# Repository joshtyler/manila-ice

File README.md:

# manila iCE

manila iCE is a credit card sized Lattice iCE40 development board.

Quick links:
* [Schematic](https://github.com/joshtyler/manila-ice/releases/download/hardware_v1.0/manila_ice-schematic.pdf)
* [Gerbers](https://github.com/joshtyler/manila-ice/releases/download/hardware_v1.0/manila_ice-fab.zip)

Features:
* Credit card sized (85x54mm)
* iCE40 HX4K FPGA (usable as an 8k device in yosys)
* Gigabit Ethernet
* 128Mbit SDRAM
* Two dual row PMODs
* 128Mbit QSPI flash
* USB UART (2Mbaud speed)
* 50MHz oscillator
* 64kbit I2C EEPROM
* 8 LEDs
* 2 push buttons
* 3A 3V3 and 1V2 power supplies

## Bootloader

The board has a bootloader which supports loading of FPGA bitstreams over UART. Four slots for bitstreams are supported. The first is reserved for the bootloader itself, and the other three can hold user images.

The FPGA is configured with the bootloader on powerup, and then automatically boots into the first bitstream after a timeout. Alternate bitstreams can be selected using the buttons, or by UART command.

## Example applications

The following applications are provided to demonstrate functionality of the PCB:
* UART loopback
* SDRAM controller
* Gigabit ethernet loopback

## Programming Application

To support uploading user applications, a Linux software utility is provided to update any of the bitstream slots.

To install the software checkout this repository, and run the following commands:
1. `cd sw/scripts`
1. `make`
1. `make install`

You will now have an executable called `manila` in your path.

To program the FPGA:
1. Plug in the board with USB
1. Press either of the switches to pause the boot process (optional if you're quick!)
1. `manila prog [path to bitstream]`

To discover the optional arguments run `manila prog` without any arguments.

## SPI Flash

The SPI flash memory is laid out as follows:

The bootloader partition is protected to prevent accidental erasure.

## Bootloader Upgrades

In order to allow for firmware upgrades the protection is volatile. When the firmware is configured with the bootloader, before UART commands are accpeted it sends commands to the SPI flash to write protect the bootloader region, and then locks out that configuration until the SPI flash is power cycled.

TODO: document process for upgrading bootloader

## PCB Errata
* v1.0 - No known issues affecting functionality
	* LEDs in ethernet phy do not light due to symbol error
	* Silkscreen box around phtograph on back does not fully enclose image after fab
	* Caption for photograph on back is difficult to read

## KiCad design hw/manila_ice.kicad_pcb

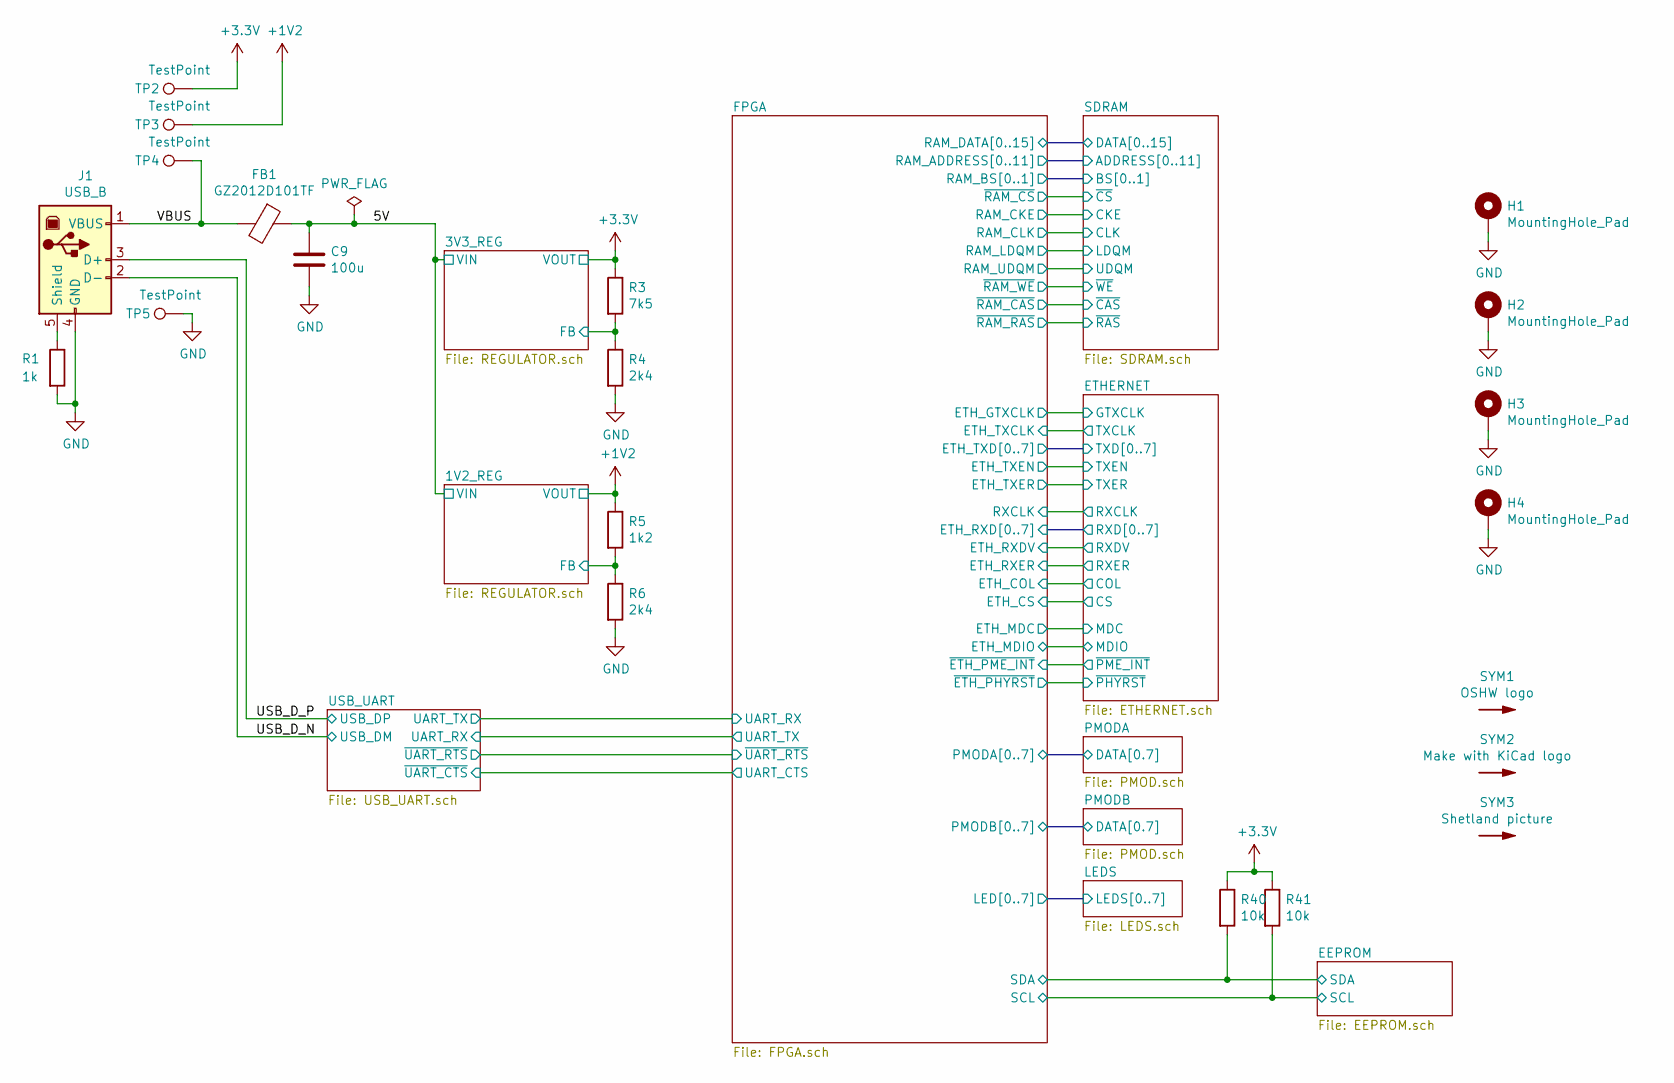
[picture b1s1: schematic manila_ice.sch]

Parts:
C9: 100u; CP_EIA-3528-21_Kemet-B; LCSC Part C16133
FB1: GZ2012D101TF; L_0805_2012Metric; LCSC Part C1015
H1, H2, H3, H4: MountingHole_Pad; MountingHole_3.2mm_M3_Pad; JLCPCB BOM 0
J1: USB_B; USB_B_OST_USB-B1HSxx_Horizontal; JLCPCB BOM 0
R1: 1k; R_0603_1608Metric; LCSC Part C21190
R3: 7k5; R_0603_1608Metric; LCSC Part C22452
R4, R6: 2k4; R_0603_1608Metric; LCSC Part C22940
R5: 1k2; R_0603_1608Metric; LCSC Part C22765
R40, R41: 10k; R_0603_1608Metric; LCSC Part C25804
SYM1: OSHW logo; OSHW-Logo_5.7x6mm_SilkScreen; JLCPCB BOM 0
SYM2: Make with KiCad logo; KiCad-Logo2_5mm_SilkScreen; JLCPCB BOM 0
SYM3: Shetland picture; Shetland_combined; JLCPCB BOM 0
TP2, TP3, TP4, TP5: TestPoint; TestPoint_Pad_D1.0mm; JLCPCB BOM 0

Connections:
+1V2: R5.1, TP3.1; also elsewhere on the board
/1V2_REG/FB: R5.2, R6.1; also elsewhere on the board
/3V3_REG/FB: R3.2, R4.1; also elsewhere on the board
/5V: C9.1, FB1.1; also elsewhere on the board
/EEPROM/SCL: R41.2; also elsewhere on the board
/EEPROM/SDA: R40.2; also elsewhere on the board
/USB_D_N: J1.2 (D-); also elsewhere on the board
/USB_D_P: J1.3 (D+); also elsewhere on the board
/VBUS: FB1.2, J1.1 (VBUS), TP4.1
GND: C9.2, H1.1, H2.1, H3.1, H4.1, J1.4 (GND), R1.2, R4.2, R6.2, TP5.1; also elsewhere on the board
unnamed: J1.5 (Shield), R1.1

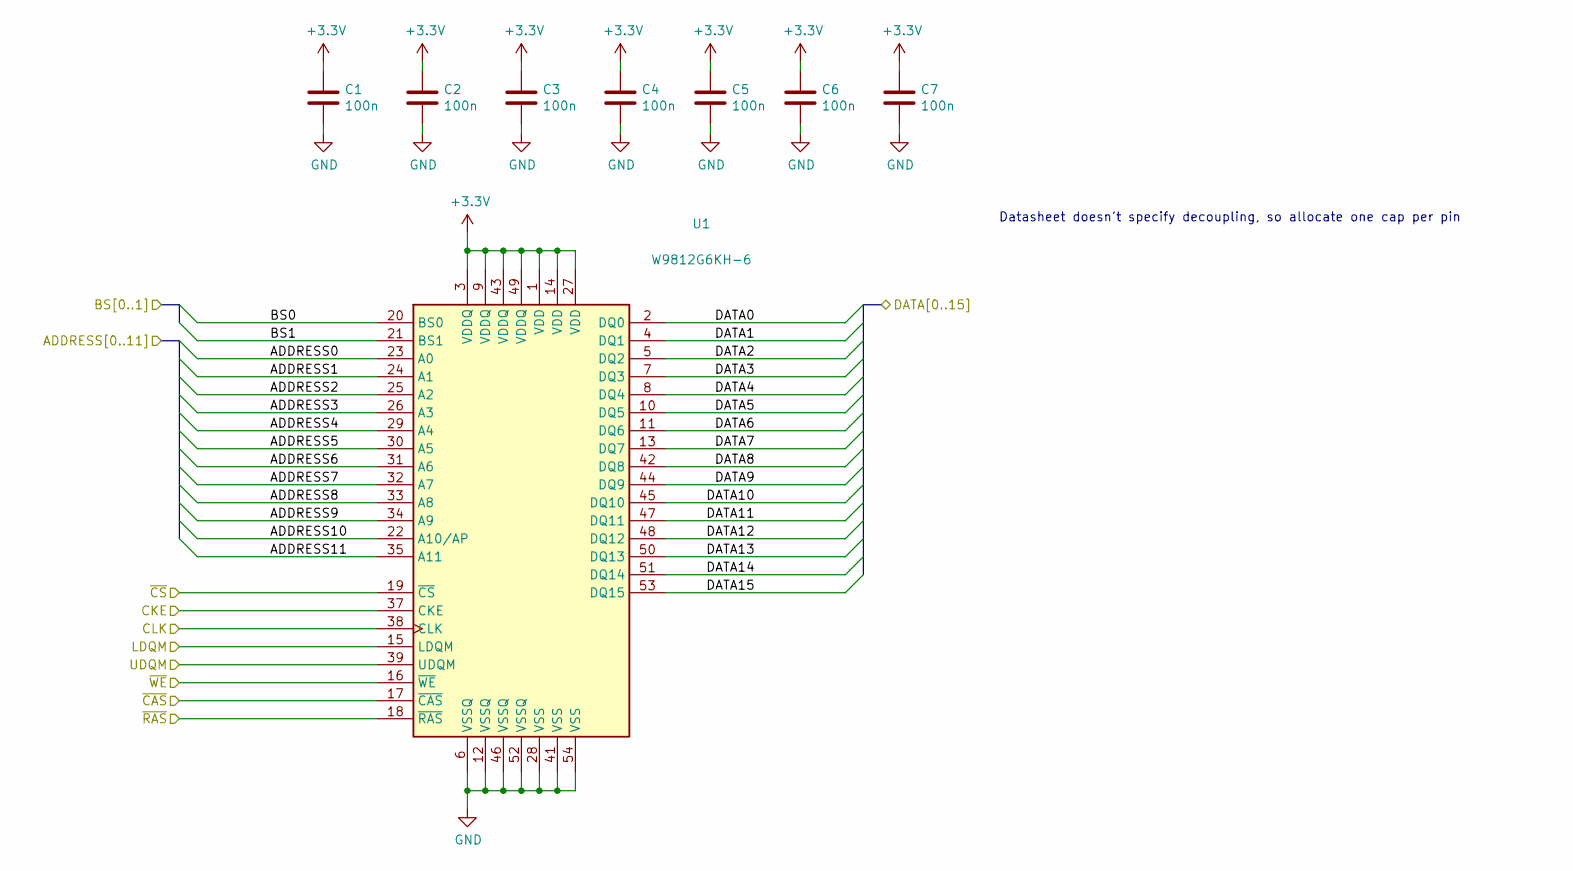
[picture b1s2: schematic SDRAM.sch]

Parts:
C1, C2, C3, C4, C5, C6, C7: 100n; C_0603_1608Metric; LCSC Part C14663
U1: W9812G6KH-6; TSOP-II-54_22.2x10.16mm_P0.8mm; LCSC Part C62379

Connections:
/FPGA/RAM_UDQM: U1.39 (UDQM); also elsewhere on the board
/FPGA/~RAM_RAS: U1.18 (~RAS); also elsewhere on the board
/FPGA/~RAM_WE: U1.16 (~WE); also elsewhere on the board
/SDRAM/ADDRESS0: U1.23 (A0); also elsewhere on the board
/SDRAM/ADDRESS1: U1.24 (A1); also elsewhere on the board
/SDRAM/ADDRESS2: U1.25 (A2); also elsewhere on the board
/SDRAM/ADDRESS3: U1.26 (A3); also elsewhere on the board
/SDRAM/ADDRESS4: U1.29 (A4); also elsewhere on the board
/SDRAM/ADDRESS5: U1.30 (A5); also elsewhere on the board
/SDRAM/ADDRESS6: U1.31 (A6); also elsewhere on the board
/SDRAM/ADDRESS7: U1.32 (A7); also elsewhere on the board
/SDRAM/ADDRESS8: U1.33 (A8); also elsewhere on the board
/SDRAM/ADDRESS9: U1.34 (A9); also elsewhere on the board
/SDRAM/ADDRESS10: U1.22 (A10/AP); also elsewhere on the board
/SDRAM/ADDRESS11: U1.35 (A11); also elsewhere on the board
/SDRAM/BS0: U1.20 (BS0); also elsewhere on the board
/SDRAM/BS1: U1.21 (BS1); also elsewhere on the board
/SDRAM/CKE: U1.37 (CKE); also elsewhere on the board
/SDRAM/CLK: U1.38 (CLK); also elsewhere on the board
/SDRAM/DATA0: U1.2 (DQ0); also elsewhere on the board
/SDRAM/DATA1: U1.4 (DQ1); also elsewhere on the board
/SDRAM/DATA2: U1.5 (DQ2); also elsewhere on the board
/SDRAM/DATA3: U1.7 (DQ3); also elsewhere on the board
/SDRAM/DATA4: U1.8 (DQ4); also elsewhere on the board
/SDRAM/DATA5: U1.10 (DQ5); also elsewhere on the board
/SDRAM/DATA6: U1.11 (DQ6); also elsewhere on the board
/SDRAM/DATA7: U1.13 (DQ7); also elsewhere on the board
/SDRAM/DATA8: U1.42 (DQ8); also elsewhere on the board
/SDRAM/DATA9: U1.44 (DQ9); also elsewhere on the board
/SDRAM/DATA10: U1.45 (DQ10); also elsewhere on the board
/SDRAM/DATA11: U1.47 (DQ11); also elsewhere on the board
/SDRAM/DATA12: U1.48 (DQ12); also elsewhere on the board
/SDRAM/DATA13: U1.50 (DQ13); also elsewhere on the board
/SDRAM/DATA14: U1.51 (DQ14); also elsewhere on the board
/SDRAM/DATA15: U1.53 (DQ15); also elsewhere on the board
/SDRAM/LDQM: U1.15 (LDQM); also elsewhere on the board
/SDRAM/~CAS: U1.17 (~CAS); also elsewhere on the board
/SDRAM/~CS: U1.19 (~CS); also elsewhere on the board
GND: C1.2, C2.2, C3.2, C4.2, C5.2, C6.2, C7.2, U1.6 (VSSQ), U1.12 (VSSQ), U1.28 (VSS), U1.41 (VSS), U1.46 (VSSQ), U1.52 (VSSQ), U1.54 (VSS); also elsewhere on the board

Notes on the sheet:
Datasheet doesn't specify decoupling, so allocate one cap per pin

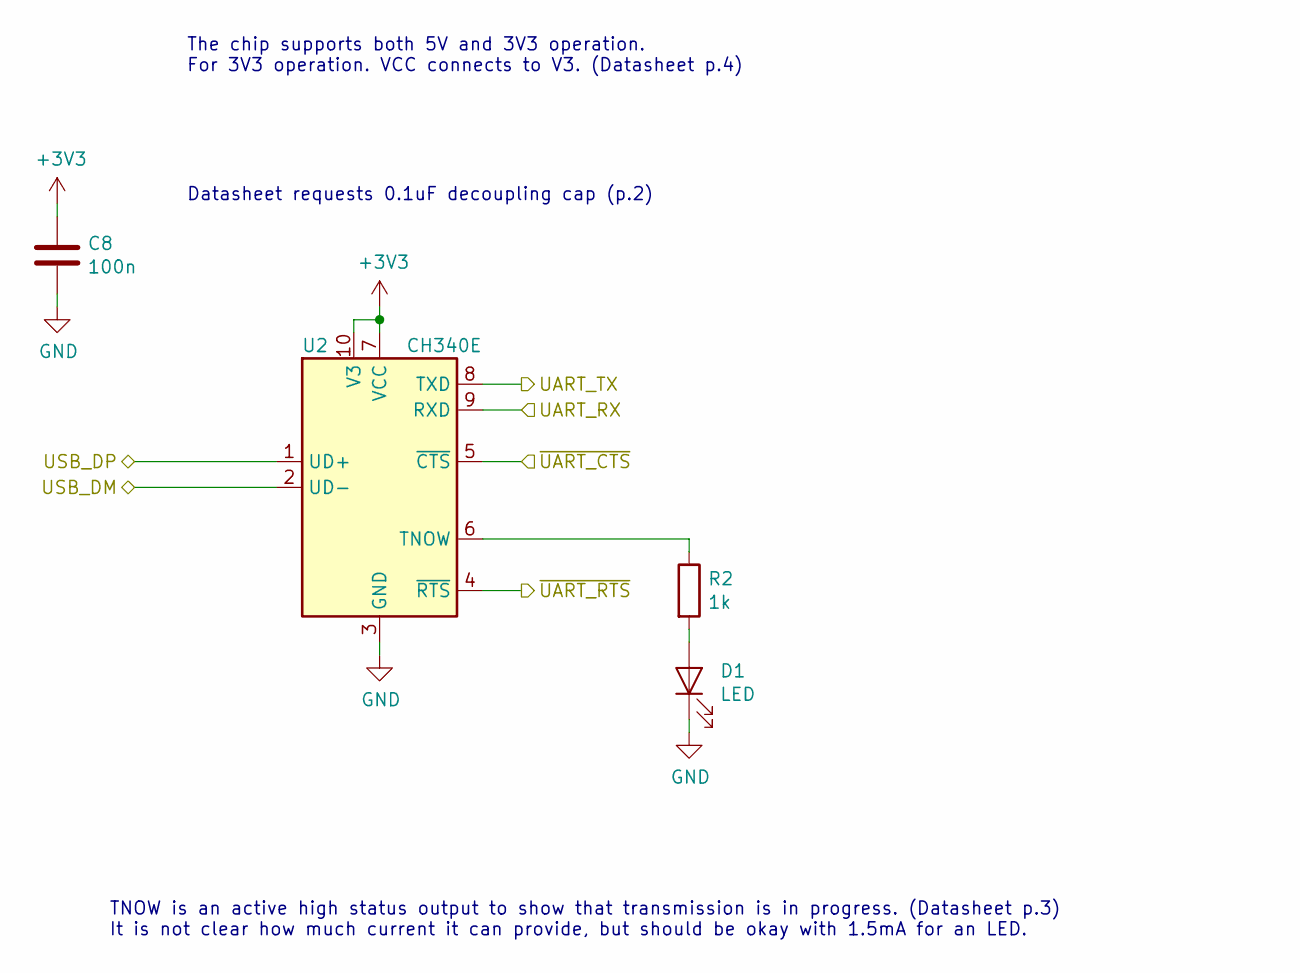
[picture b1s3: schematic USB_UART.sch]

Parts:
C8: 100n; C_0603_1608Metric; LCSC Part C14663
D1: LED; D_0805_2012Metric_Castellated; LCSC Part C84256
R2: 1k; R_0603_1608Metric; LCSC Part C21190
U2: CH340E; MSOP-10_3x3mm_P0.5mm; JLCPCB Rotation -90

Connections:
/FPGA/UART_CTS: U2.5 (~CTS); also elsewhere on the board
/FPGA/UART_RX: U2.8 (TXD); also elsewhere on the board
/FPGA/~UART_RTS: U2.4 (~RTS); also elsewhere on the board
/USB_D_N: U2.2 (UD-); also elsewhere on the board
/USB_D_P: U2.1 (UD+); also elsewhere on the board
/USB_UART/UART_RX: U2.9 (RXD); also elsewhere on the board
GND: C8.2, D1.1 (K), U2.3 (GND); also elsewhere on the board
unnamed: D1.2 (A), R2.2
unnamed: R2.1, U2.6 (TNOW)

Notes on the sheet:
TNOW is an active high status output to show that transmission is in progress. (Datasheet p.3) It is not clear how much current it can provide, but should be okay with 1.5mA for an LED.
The chip supports both 5V and 3V3 operation. For 3V3 operation. VCC connects to V3. (Datasheet p.4)
Datasheet requests 0.1uF decoupling cap (p.2)

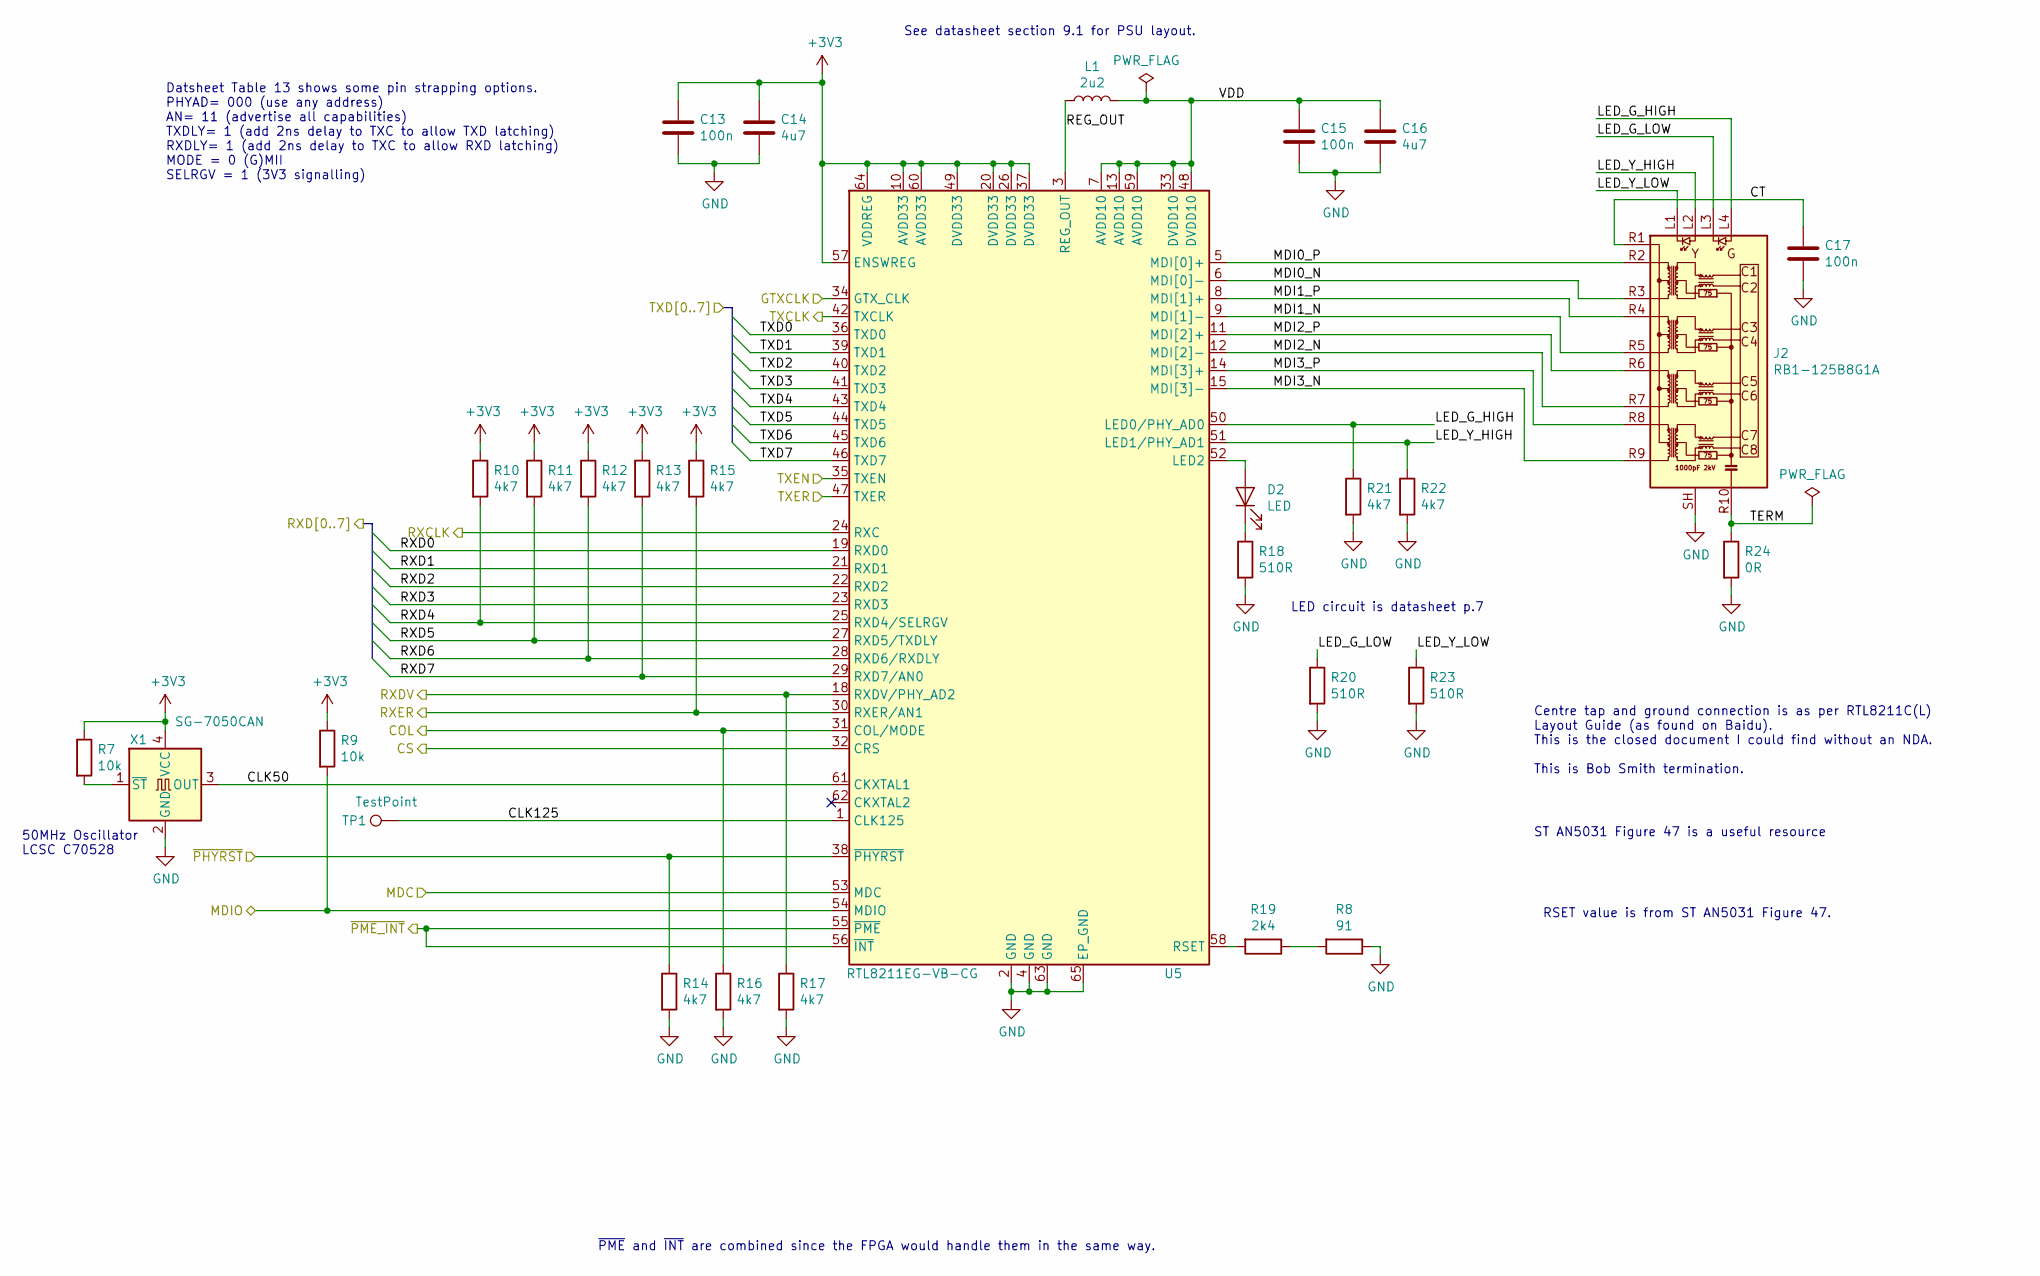
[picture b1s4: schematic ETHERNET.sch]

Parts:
C13, C15, C17: 100n; C_0603_1608Metric; LCSC Part C14663
C14, C16: 4u7; C_0603_1608Metric; LCSC Part C19666
D2: LED; D_0805_2012Metric_Castellated; LCSC Part C84256
J2: RB1-125B8G1A; RJ45_UDE_RB1-125B8G1A; JLCPCB BOM 0
L1: 2u2; L_Sunlord_MWSA0518; LCSC Part C408345
R7, R9: 10k; R_0603_1608Metric; LCSC Part C25804
R8: 91; R_0603_1608Metric; LCSC Part C25199
R10, R11, R12, R13, R14, R15, R16, R17, R21, R22: 4k7; R_0603_1608Metric; LCSC Part C23162
R18, R20, R23: 510R; R_0603_1608Metric; LCSC Part C23193
R19: 2k4; R_0603_1608Metric; LCSC Part C22940
R24: 0R; R_0603_1608Metric; LCSC Part C21189
TP1: TestPoint; TestPoint_Pad_D1.0mm; JLCPCB BOM 0
U5: RTL8211EG-VB-CG; QFN-64-1EP_9x9mm_P0.5mm_EP3.8x3.8mm_ThermalVias; LCSC Part C69264
X1: SG-7050CAN; Oscillator_SMD_SeikoEpson_SG8002CA-4Pin_7.0x5.0mm; LCSC Part C70528

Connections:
/ETHERNET/CLK50: U5.61 (CKXTAL1), X1.3 (OUT)
/ETHERNET/CLK125: TP1.1, U5.1 (CLK125)
/ETHERNET/COL: R16.1, U5.31 (COL/MODE); also elsewhere on the board
/ETHERNET/CS: U5.32 (CRS); also elsewhere on the board
/ETHERNET/CT: C17.1, J2.R1 (CT)
/ETHERNET/LED_G_HIGH: J2.L4, R21.1, U5.50 (LED0/PHY_AD0)
/ETHERNET/LED_G_LOW: J2.L3, R20.1
/ETHERNET/LED_Y_HIGH: J2.L2, R22.1, U5.51 (LED1/PHY_AD1)
/ETHERNET/LED_Y_LOW: J2.L1, R23.1
/ETHERNET/MDI0_N: J2.R3 (TD1-), U5.6 (MDI[0]-)
/ETHERNET/MDI0_P: J2.R2 (TD1+), U5.5 (MDI[0]+)
/ETHERNET/MDI1_N: J2.R5 (TD2-), U5.9 (MDI[1]-)
/ETHERNET/MDI1_P: J2.R4 (TD2+), U5.8 (MDI[1]+)
/ETHERNET/MDI2_N: J2.R7 (TD3-), U5.12 (MDI[2]-)
/ETHERNET/MDI2_P: J2.R6 (TD3+), U5.11 (MDI[2]+)
/ETHERNET/MDI3_N: J2.R9 (TD4-), U5.15 (MDI[3]-)
/ETHERNET/MDI3_P: J2.R8 (TD4+), U5.14 (MDI[3]+)
/ETHERNET/REG_OUT: L1.1, U5.3 (REG_OUT)
/ETHERNET/RXCLK: U5.24 (RXC); also elsewhere on the board
/ETHERNET/TERM: J2.R10 (GND), R24.1
/ETHERNET/VDD: C15.1, C16.1, L1.2, U5.7 (AVDD10), U5.13 (AVDD10), U5.33 (DVDD10), U5.48 (DVDD10), U5.59 (AVDD10)
/FPGA/ETH_GTXCLK: U5.34 (GTX_CLK); also elsewhere on the board
/FPGA/ETH_MDC: U5.53 (MDC); also elsewhere on the board
/FPGA/ETH_MDIO: R9.2, U5.54 (MDIO); also elsewhere on the board
/FPGA/ETH_RXD0: U5.19 (RXD0); also elsewhere on the board
/FPGA/ETH_RXD1: U5.21 (RXD1); also elsewhere on the board
/FPGA/ETH_RXD2: U5.22 (RXD2); also elsewhere on the board
/FPGA/ETH_RXD3: U5.23 (RXD3); also elsewhere on the board
/FPGA/ETH_RXD4: R10.2, U5.25 (RXD4/SELRGV); also elsewhere on the board
/FPGA/ETH_RXD5: R11.2, U5.27 (RXD5/TXDLY); also elsewhere on the board
/FPGA/ETH_RXD6: R12.2, U5.28 (RXD6/RXDLY); also elsewhere on the board
/FPGA/ETH_RXD7: R13.2, U5.29 (RXD7/AN0); also elsewhere on the board
/FPGA/ETH_RXDV: R17.1, U5.18 (RXDV/PHY_AD2); also elsewhere on the board
/FPGA/ETH_RXER: R15.2, U5.30 (RXER/AN1); also elsewhere on the board
/FPGA/ETH_TXCLK: U5.42 (TXCLK); also elsewhere on the board
/FPGA/ETH_TXD0: U5.36 (TXD0); also elsewhere on the board
/FPGA/ETH_TXD1: U5.39 (TXD1); also elsewhere on the board
/FPGA/ETH_TXD2: U5.40 (TXD2); also elsewhere on the board
/FPGA/ETH_TXD3: U5.41 (TXD3); also elsewhere on the board
/FPGA/ETH_TXD4: U5.43 (TXD4); also elsewhere on the board
/FPGA/ETH_TXD5: U5.44 (TXD5); also elsewhere on the board
/FPGA/ETH_TXD6: U5.45 (TXD6); also elsewhere on the board
/FPGA/ETH_TXD7: U5.46 (TXD7); also elsewhere on the board
/FPGA/ETH_TXEN: U5.35 (TXEN); also elsewhere on the board
/FPGA/ETH_TXER: U5.47 (TXER); also elsewhere on the board
/FPGA/~ETH_PHYRST: R14.1, U5.38 (~PHYRST); also elsewhere on the board
/FPGA/~ETH_PME_INT: U5.55 (~PME), U5.56 (~INT); also elsewhere on the board
GND: C13.2, C14.2, C15.2, C16.2, C17.2, J2.SH, R8.1, R14.2, R16.2, R17.2, R18.2, R20.2, R21.2, R22.2, R23.2, R24.2, U5.2 (GND), U5.4 (GND), U5.63 (GND), U5.65 (EP_GND), X1.2 (GND); also elsewhere on the board
unnamed: D2.1 (K), R18.1
unnamed: D2.2 (A), U5.52 (LED2)
unnamed: R7.2, X1.1 (~ST)
unnamed: R8.2, R19.1
unnamed: R19.2, U5.58 (RSET)

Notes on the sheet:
See datasheet section 9.1 for PSU layout.
50MHz Oscillator LCSC C70528
~PME~ and ~INT~ are combined since the FPGA would handle them in the same way.
Centre tap and ground connection is as per RTL8211C(L) Layout Guide (as found on Baidu). This is the closed document I could find without an NDA. This is Bob Smith termination.
LED circuit is datasheet p.7
Datsheet Table 13 shows some pin strapping options. PHYAD= 000 (use any address) AN= 11 (advertise all capabilities) TXDLY= 1 (add 2ns delay to TXC to allow TXD latching) RXDLY= 1 (add 2ns delay to TXC to allow RXD latching) MODE = 0 (G)MII SELRGV = 1 (3V3 signalling)
ST AN5031 Figure 47 is a useful resource
RSET value is from ST AN5031 Figure 47.

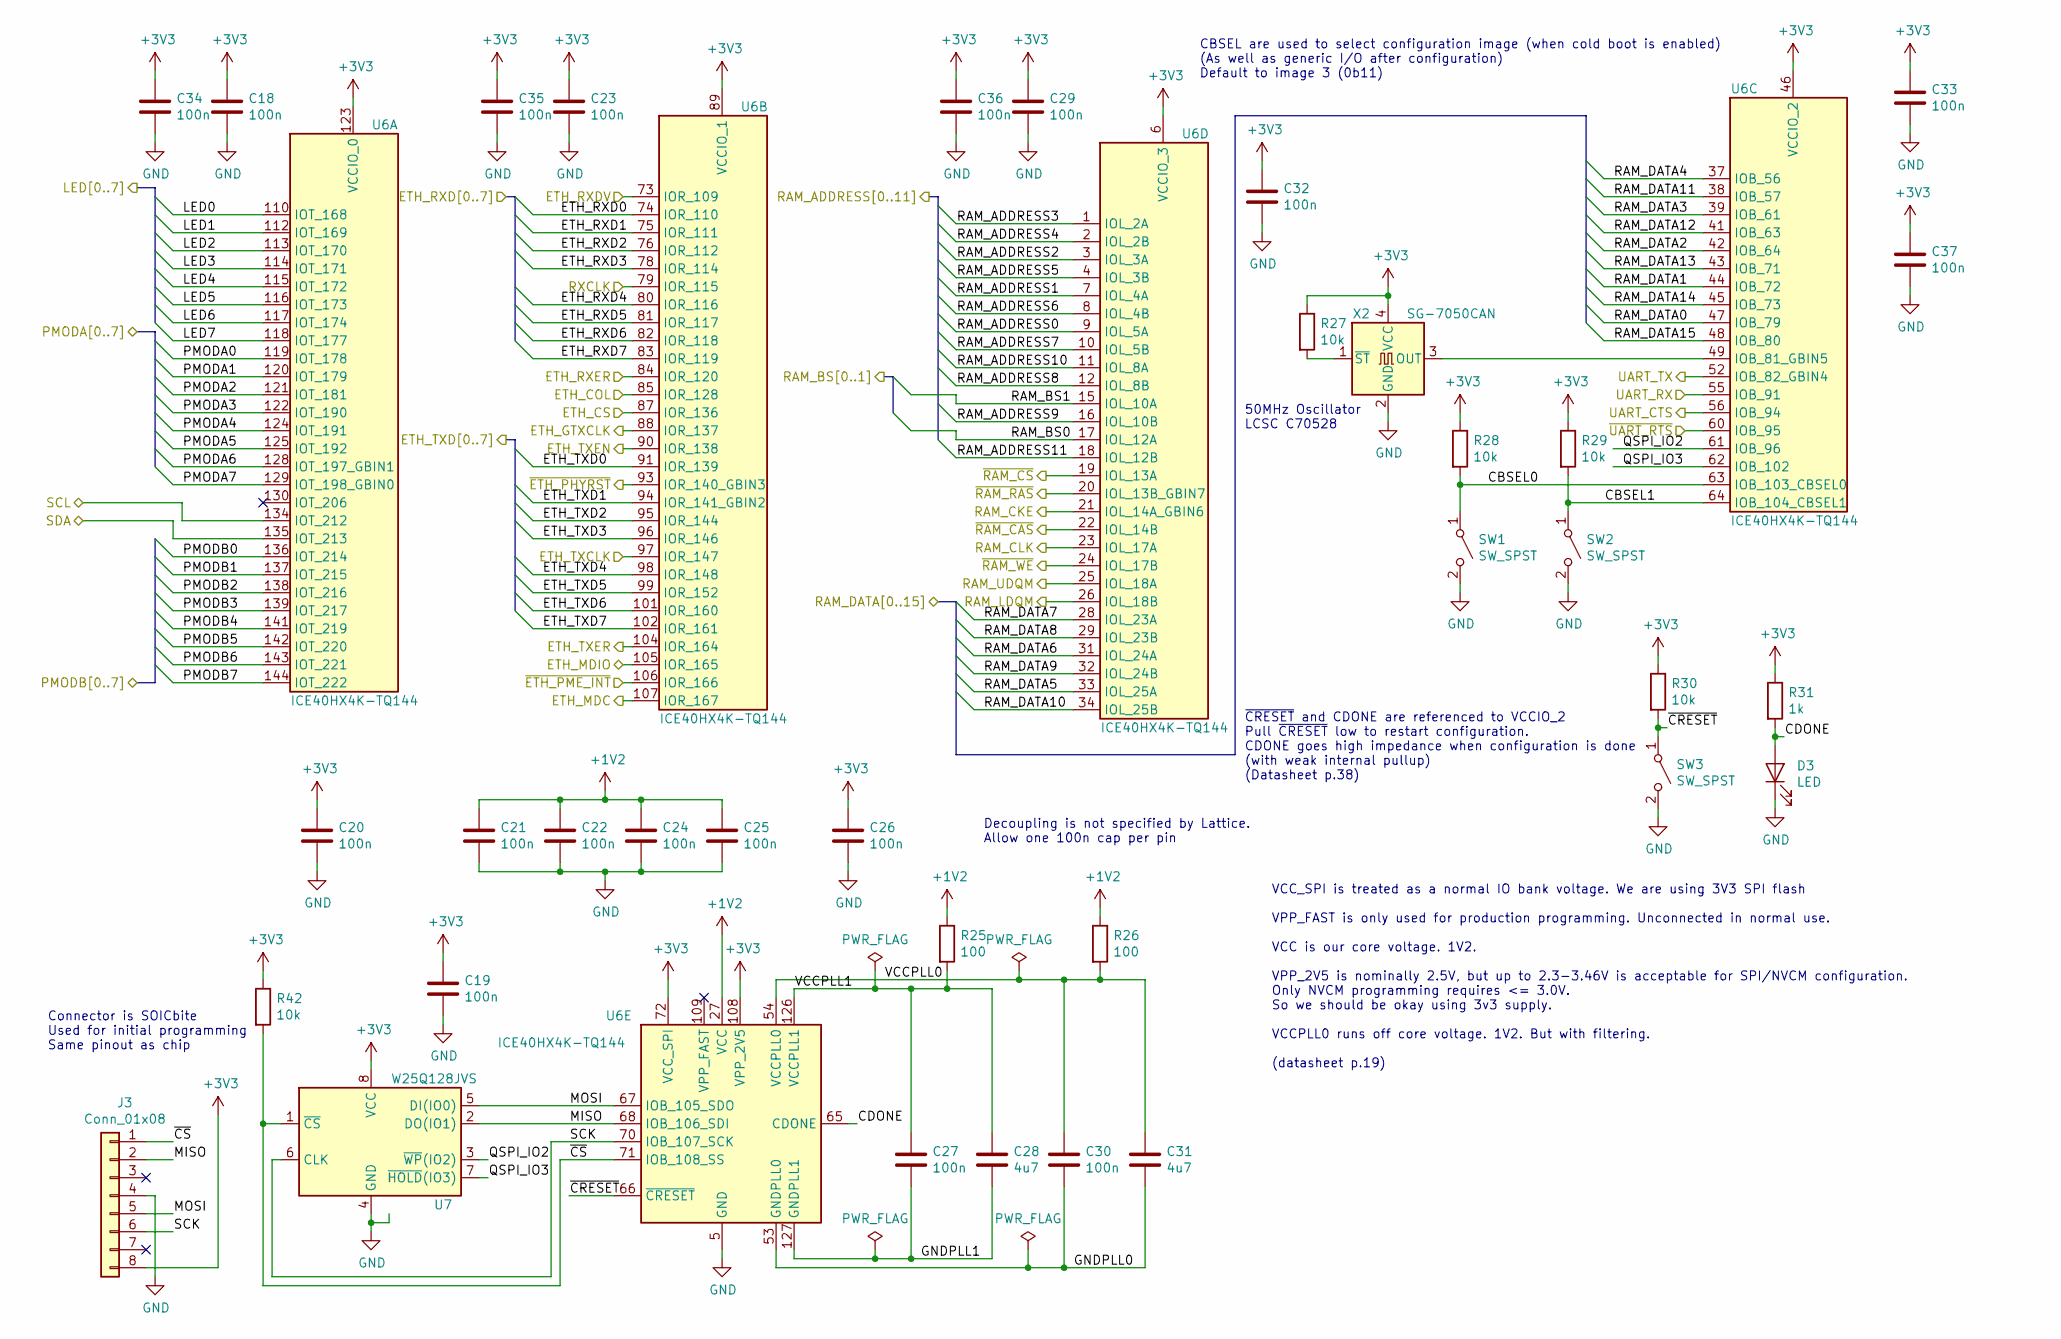
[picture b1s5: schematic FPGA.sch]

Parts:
C18, C19, C20, C21, C22, C23, C24, C25, C26, C27, C29, C30, C32, C33, C34, C35, C36, C37: 100n; C_0603_1608Metric; LCSC Part C14663
C28, C31: 4u7; C_0603_1608Metric; LCSC Part C19666
D3: LED; D_0805_2012Metric_Castellated; LCSC Part C84256
J3: Conn_01x08; SOIC_clipProgSmall; JLCPCB BOM 0
R25, R26: 100; R_0603_1608Metric; LCSC Part C22775
R27, R28, R29, R30, R42: 10k; R_0603_1608Metric; LCSC Part C25804
R31: 1k; R_0603_1608Metric; LCSC Part C21190
SW1, SW2, SW3: SW_SPST; SW_Push_1P1T_NO_5.1x5.1mm; LCSC Part C318888
U6: ICE40HX4K-TQ144; TQFP-144_20x20mm_P0.5mm; JLCPCB BOM 0
U7: W25Q128JVS; SOIC-8_5.23x5.23mm_P1.27mm; LCSC Part C97521
X2: SG-7050CAN; Oscillator_SMD_SeikoEpson_SG8002CA-4Pin_7.0x5.0mm; LCSC Part C70528

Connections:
+1V2: C21.1, C22.1, C24.1, C25.1, R25.1, R26.1, U6.27 (VCC), U6.40 (VCC), U6.92 (VCC), U6.111 (VCC); also elsewhere on the board
/EEPROM/SCL: U6.134 (IOT_212); also elsewhere on the board
/EEPROM/SDA: U6.135 (IOT_213); also elsewhere on the board
/ETHERNET/COL: U6.85 (IOR_128); also elsewhere on the board
/ETHERNET/CS: U6.87 (IOR_136); also elsewhere on the board
/ETHERNET/RXCLK: U6.79 (IOR_115); also elsewhere on the board
/FPGA/CBSEL0: R28.2, SW1.1 (A), U6.63 (IOB_103_CBSEL0)
/FPGA/CBSEL1: R29.2, SW2.1 (A), U6.64 (IOB_104_CBSEL1)
/FPGA/CDONE: D3.2 (A), R31.2, U6.65 (CDONE)
/FPGA/ETH_GTXCLK: U6.88 (IOR_137); also elsewhere on the board
/FPGA/ETH_MDC: U6.107 (IOR_167); also elsewhere on the board
/FPGA/ETH_MDIO: U6.105 (IOR_165); also elsewhere on the board
/FPGA/ETH_RXD0: U6.74 (IOR_110); also elsewhere on the board
/FPGA/ETH_RXD1: U6.75 (IOR_111); also elsewhere on the board
/FPGA/ETH_RXD2: U6.76 (IOR_112); also elsewhere on the board
/FPGA/ETH_RXD3: U6.78 (IOR_114); also elsewhere on the board
/FPGA/ETH_RXD4: U6.80 (IOR_116); also elsewhere on the board
/FPGA/ETH_RXD5: U6.81 (IOR_117); also elsewhere on the board
/FPGA/ETH_RXD6: U6.82 (IOR_118); also elsewhere on the board
/FPGA/ETH_RXD7: U6.83 (IOR_119); also elsewhere on the board
/FPGA/ETH_RXDV: U6.73 (IOR_109); also elsewhere on the board
/FPGA/ETH_RXER: U6.84 (IOR_120); also elsewhere on the board
/FPGA/ETH_TXCLK: U6.97 (IOR_147); also elsewhere on the board
/FPGA/ETH_TXD0: U6.91 (IOR_139); also elsewhere on the board
/FPGA/ETH_TXD1: U6.94 (IOR_141_GBIN2); also elsewhere on the board
/FPGA/ETH_TXD2: U6.95 (IOR_144); also elsewhere on the board
/FPGA/ETH_TXD3: U6.96 (IOR_146); also elsewhere on the board
/FPGA/ETH_TXD4: U6.98 (IOR_148); also elsewhere on the board
/FPGA/ETH_TXD5: U6.99 (IOR_152); also elsewhere on the board
/FPGA/ETH_TXD6: U6.101 (IOR_160); also elsewhere on the board
/FPGA/ETH_TXD7: U6.102 (IOR_161); also elsewhere on the board
/FPGA/ETH_TXEN: U6.90 (IOR_138); also elsewhere on the board
/FPGA/ETH_TXER: U6.104 (IOR_164); also elsewhere on the board
/FPGA/GNDPLL0: C30.2, C31.2, U6.53 (GNDPLL0)
/FPGA/GNDPLL1: C27.2, C28.2, U6.127 (GNDPLL1)
/FPGA/LED0: U6.110 (IOT_168); also elsewhere on the board
/FPGA/LED1: U6.112 (IOT_169); also elsewhere on the board
/FPGA/LED2: U6.113 (IOT_170); also elsewhere on the board
/FPGA/LED3: U6.114 (IOT_171); also elsewhere on the board
/FPGA/LED4: U6.115 (IOT_172); also elsewhere on the board
/FPGA/LED5: U6.116 (IOT_173); also elsewhere on the board
/FPGA/LED6: U6.117 (IOT_174); also elsewhere on the board
/FPGA/LED7: U6.118 (IOT_177); also elsewhere on the board
/FPGA/MISO: J3.2, U6.68 (IOB_106_SDI), U7.2 (DO(IO1))
/FPGA/MOSI: J3.5, U6.67 (IOB_105_SDO), U7.5 (DI(IO0))
/FPGA/QSPI_IO2: U6.61 (IOB_96), U7.3 (~WP~(IO2))
/FPGA/QSPI_IO3: U6.62 (IOB_102), U7.7 (~HOLD~(IO3))
/FPGA/RAM_UDQM: U6.25 (IOL_18A); also elsewhere on the board
/FPGA/SCK: J3.6, U6.70 (IOB_107_SCK), U7.6 (CLK)
/FPGA/UART_CTS: U6.56 (IOB_94); also elsewhere on the board
/FPGA/UART_RX: U6.55 (IOB_91); also elsewhere on the board
/FPGA/VCCPLL0: C30.1, C31.1, R26.2, U6.54 (VCCPLL0)
/FPGA/VCCPLL1: C27.1, C28.1, R25.2, U6.126 (VCCPLL1)
/FPGA/~CRESET: R30.2, SW3.1 (A), U6.66 (~CRESET)
/FPGA/~CS: J3.1, R42.2, U6.71 (IOB_108_SS), U7.1 (~CS)
/FPGA/~ETH_PHYRST: U6.93 (IOR_140_GBIN3); also elsewhere on the board
/FPGA/~ETH_PME_INT: U6.106 (IOR_166); also elsewhere on the board
/FPGA/~RAM_RAS: U6.20 (IOL_13B_GBIN7); also elsewhere on the board
/FPGA/~RAM_WE: U6.24 (IOL_17B); also elsewhere on the board
/FPGA/~UART_RTS: U6.60 (IOB_95); also elsewhere on the board
/PMODA/DATA0: U6.119 (IOT_178); also elsewhere on the board
/PMODA/DATA1: U6.120 (IOT_179); also elsewhere on the board
/PMODA/DATA2: U6.121 (IOT_181); also elsewhere on the board
/PMODA/DATA3: U6.122 (IOT_190); also elsewhere on the board
/PMODA/DATA4: U6.124 (IOT_191); also elsewhere on the board
/PMODA/DATA5: U6.125 (IOT_192); also elsewhere on the board
/PMODA/DATA6: U6.128 (IOT_197_GBIN1); also elsewhere on the board
/PMODA/DATA7: U6.129 (IOT_198_GBIN0); also elsewhere on the board
/PMODB/DATA0: U6.136 (IOT_214); also elsewhere on the board
/PMODB/DATA1: U6.137 (IOT_215); also elsewhere on the board
/PMODB/DATA2: U6.138 (IOT_216); also elsewhere on the board
/PMODB/DATA3: U6.139 (IOT_217); also elsewhere on the board
/PMODB/DATA4: U6.141 (IOT_219); also elsewhere on the board
/PMODB/DATA5: U6.142 (IOT_220); also elsewhere on the board
/PMODB/DATA6: U6.143 (IOT_221); also elsewhere on the board
/PMODB/DATA7: U6.144 (IOT_222); also elsewhere on the board
/SDRAM/ADDRESS0: U6.9 (IOL_5A); also elsewhere on the board
/SDRAM/ADDRESS1: U6.7 (IOL_4A); also elsewhere on the board
/SDRAM/ADDRESS2: U6.3 (IOL_3A); also elsewhere on the board
/SDRAM/ADDRESS3: U6.1 (IOL_2A); also elsewhere on the board
/SDRAM/ADDRESS4: U6.2 (IOL_2B); also elsewhere on the board
/SDRAM/ADDRESS5: U6.4 (IOL_3B); also elsewhere on the board
/SDRAM/ADDRESS6: U6.8 (IOL_4B); also elsewhere on the board
/SDRAM/ADDRESS7: U6.10 (IOL_5B); also elsewhere on the board
/SDRAM/ADDRESS8: U6.12 (IOL_8B); also elsewhere on the board
/SDRAM/ADDRESS9: U6.16 (IOL_10B); also elsewhere on the board
/SDRAM/ADDRESS10: U6.11 (IOL_8A); also elsewhere on the board
/SDRAM/ADDRESS11: U6.18 (IOL_12B); also elsewhere on the board
/SDRAM/BS0: U6.17 (IOL_12A); also elsewhere on the board
/SDRAM/BS1: U6.15 (IOL_10A); also elsewhere on the board
/SDRAM/CKE: U6.21 (IOL_14A_GBIN6); also elsewhere on the board
/SDRAM/CLK: U6.23 (IOL_17A); also elsewhere on the board
/SDRAM/DATA0: U6.47 (IOB_79); also elsewhere on the board
/SDRAM/DATA1: U6.44 (IOB_72); also elsewhere on the board
/SDRAM/DATA2: U6.42 (IOB_64); also elsewhere on the board
/SDRAM/DATA3: U6.39 (IOB_61); also elsewhere on the board
/SDRAM/DATA4: U6.37 (IOB_56); also elsewhere on the board
/SDRAM/DATA5: U6.33 (IOL_25A); also elsewhere on the board
/SDRAM/DATA6: U6.31 (IOL_24A); also elsewhere on the board
/SDRAM/DATA7: U6.28 (IOL_23A); also elsewhere on the board
/SDRAM/DATA8: U6.29 (IOL_23B); also elsewhere on the board
/SDRAM/DATA9: U6.32 (IOL_24B); also elsewhere on the board
/SDRAM/DATA10: U6.34 (IOL_25B); also elsewhere on the board
/SDRAM/DATA11: U6.38 (IOB_57); also elsewhere on the board
/SDRAM/DATA12: U6.41 (IOB_63); also elsewhere on the board
/SDRAM/DATA13: U6.43 (IOB_71); also elsewhere on the board
/SDRAM/DATA14: U6.45 (IOB_73); also elsewhere on the board
/SDRAM/DATA15: U6.48 (IOB_80); also elsewhere on the board
/SDRAM/LDQM: U6.26 (IOL_18B); also elsewhere on the board
/SDRAM/~CAS: U6.22 (IOL_14B); also elsewhere on the board
/SDRAM/~CS: U6.19 (IOL_13A); also elsewhere on the board
/USB_UART/UART_RX: U6.52 (IOB_82_GBIN4); also elsewhere on the board
GND: C18.2, C19.2, C20.2, C21.2, C22.2, C23.2, C24.2, C25.2, C26.2, C29.2, C32.2, C33.2, C34.2, C35.2, C36.2, C37.2, D3.1 (K), J3.4, SW1.2 (B), SW2.2 (B), SW3.2 (B), U6.5 (GND), U6.13 (GND), U6.14 (GND), U6.59 (GND), U6.69 (GND), U6.86 (GND), U6.103 (GND), U6.132 (GND), U6.140 (GND), U7.4 (GND), X2.2 (GND); also elsewhere on the board
unnamed: R27.2, X2.1 (~ST)
unnamed: U6.49 (IOB_81_GBIN5), X2.3 (OUT)

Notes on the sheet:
VCC_SPI is treated as a normal IO bank voltage. We are using 3V3 SPI flash VPP_FAST is only used for production programming. Unconnected in normal use. VCC is our core voltage. 1V2. VPP_2V5 is nominally 2.5V, but up to 2.3-3.46V is acceptable for SPI/NVCM configuration. Only NVCM programming requir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
Decoupling is not specified by Lattice. Allow one 100n cap per pin
Connector is SOICbite Used for initial programming Same pinout as chip
~CRESET~ and CDONE are referenced to VCCIO_2 Pull ~CRESET~ low to restart configuration. CDONE goes high impedance when configuration is done (with weak internal pullup) (Datasheet p.38)
CBSEL are used to select configuration image (when cold boot is enabled) (As well as generic I/O after configuration) Default to image 3 (0b11)
50MHz Oscillator LCSC C70528

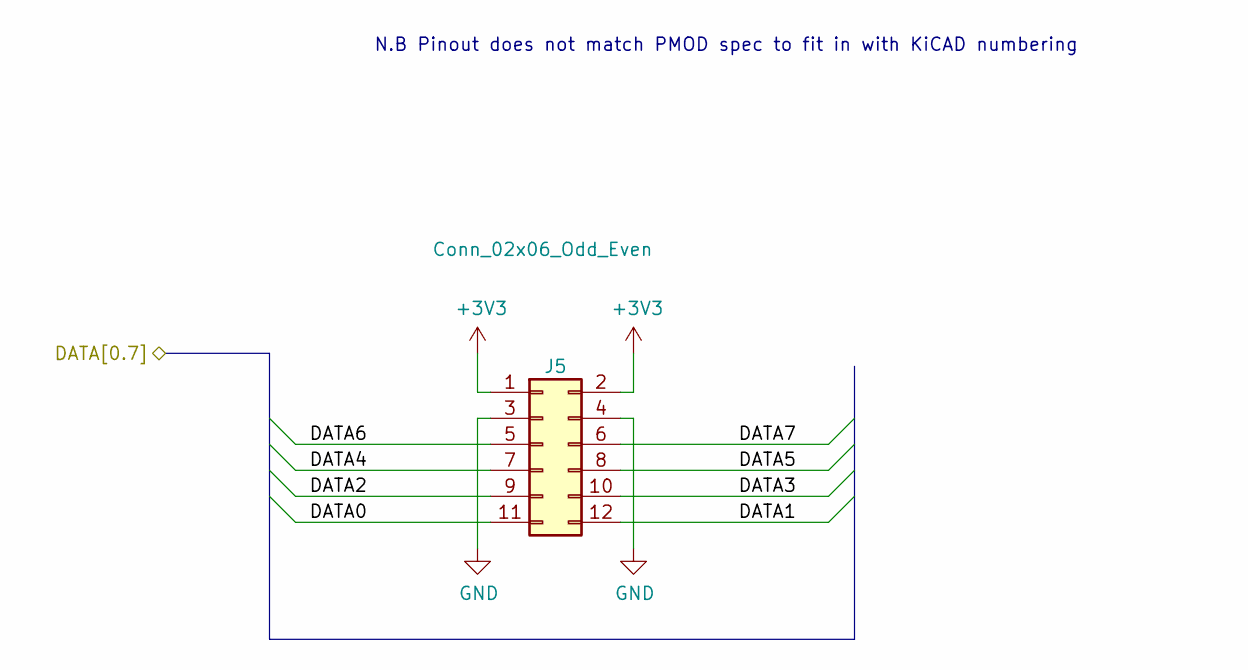
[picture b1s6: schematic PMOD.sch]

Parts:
J4: Conn_02x06_Odd_Even; PinSocket_2x06_P2.54mm_Horizontal; JLCPCB BOM 0

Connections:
/PMODA/DATA0: J4.11; also elsewhere on the board
/PMODA/DATA1: J4.12; also elsewhere on the board
/PMODA/DATA2: J4.9; also elsewhere on the board
/PMODA/DATA3: J4.10; also elsewhere on the board
/PMODA/DATA4: J4.7; also elsewhere on the board
/PMODA/DATA5: J4.8; also elsewhere on the board
/PMODA/DATA6: J4.5; also elsewhere on the board
/PMODA/DATA7: J4.6; also elsewhere on the board
GND: J4.3, J4.4; also elsewhere on the board

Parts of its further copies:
J5: Conn_02x06_Odd_Even; PinSocket_2x06_P2.54mm_Horizontal; JLCPCB BOM 0

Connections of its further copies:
/PMODB/DATA0: J5.11; also elsewhere on the board
/PMODB/DATA1: J5.12; also elsewhere on the board
/PMODB/DATA2: J5.9; also elsewhere on the board
/PMODB/DATA3: J5.10; also elsewhere on the board
/PMODB/DATA4: J5.7; also elsewhere on the board
/PMODB/DATA5: J5.8; also elsewhere on the board
/PMODB/DATA6: J5.5; also elsewhere on the board
/PMODB/DATA7: J5.6; also elsewhere on the board
GND: J5.3, J5.4; also elsewhere on the board

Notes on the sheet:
N.B Pinout does not match PMOD spec to fit in with KiCAD numbering
